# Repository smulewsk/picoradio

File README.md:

<p align="center">
  <picture>
    <source media="(prefers-color-scheme: dark)" srcset="docs/logo/logo.svg">
    
  </picture>
</p>
<p align="center"></p>

# Pico 2 W Internet Radio (FreeRTOS)

Pico Radio turns a Raspberry Pi Pico 2 W and a handful of cheap modules into a complete desktop radio. It plays internet radio stations, works as a Bluetooth speaker for your phone, and has a voice assistant you can talk to. Two knobs and a small colour display handle everyday use. A web page on your phone or computer does the rest: pick stations, edit the list, change settings and update the firmware.

**Three sources, one radio:**
- **Internet radio:** MP3 and AAC/AAC+ streams over HTTP and HTTPS, with song titles from the stream. Up to 31 stations of your own, with playlist import and export.
- **Bluetooth:** pair your phone and play its music through the radio, with artist, title and play/pause/next on the knobs.
- **AI assistant:** switch to *AI Gemini*, ask a question out loud, and hear the answer through the speaker. It uses Google's Gemini Live API on the free tier, in English or another language you choose.

**Hardware:** a Pico 2 W, a PCM5102 I2S DAC for line-level audio, a 2.25" ST7789 display (284×76), two rotary encoder modules (KY-040, or the ones labelled S1 / S2 / KEY) and, for the AI, an INMP441 microphone. Everything runs on 5 V from USB. Each module connects with a few jumper wires; see [Wiring](#wiring).

**Everyday use:**
- **Remembers you:** the radio starts on the last station at the last volume.
- **Web setup:** WiFi, names, the Gemini key and voice are set from the web page, with no rebuilding.
- **Safe updates:** firmware updates go over WiFi into a spare flash slot. If a new version fails to start, the radio falls back to the previous one.

## Screenshots

**Internet radio:** station, song title from the stream, codec, bitrate and a stereo VU meter.

**Bluetooth:** your phone's music, with artist and title.

**AI Gemini:** the spoken answer also scrolls on the display.

<p align="center"><em>The prototype on a breadboard: Pico 2 W, PCM5102 DAC with RCA outputs, two encoders, the INMP441 microphone and the display.</em></p>

## Under the hood

The firmware is written in C on FreeRTOS, using both cores of the RP2350. It was built for the Pico 2 W:

- **FreeRTOS SMP** on both cores
- **lwIP sockets** over WiFi, **HTTP and HTTPS** + Shoutcast/Icecast **ICY metadata** (song titles), redirects, **.pls / .m3u playlist links**
- **MP3 decoding** with [minimp3](https://github.com/lieff/minimp3) (32–320 kbps, mono or stereo, any sample rate)
- **AAC and HE-AAC (AAC+) decoding** with the Helix AAC decoder, for `audio/aac` and `audio/aacp` streams (ADTS)
- **PCM5102** I2S DAC driven by PIO + DMA
- **ST7789 2.25" 76×284** TFT (landscape 284×76), DMA framebuffer, SPI through PIO (any pins)
- **2 rotary encoders**: volume and station
- **Web remote**: control page at **http://picoradio.local** with a live copy of the display, a station editor and a **settings page** (WiFi, Gemini key, names... no rebuild needed)
- **WiFi setup network**: without a working WiFi the radio opens its own network (`picoradio`), and a phone that joins it lands on the settings page
- **Firmware updates over WiFi** from the web page, with automatic fallback to the previous firmware
- **Remembers** the last station and volume across power-off
- **AI voice assistant**: talk to Google Gemini through an **INMP441** microphone and hear the spoken answer on the radio (Gemini Live API, free tier). English by default, or any other language set on the web page; it greets you when you switch to it
- **Bluetooth audio (A2DP sink)**: stream from your phone. AVRCP shows the artist and title, encoder 2 controls play/pause and next track, and volume stays in sync with the phone

| Core | Task | Job |
|---|---|---|
| 0 | `net` | WiFi, HTTP/HTTPS, playlists, ICY demux → 48 KB stream buffer |
| 0 | `ui` | encoders, screen at 25 fps, saves station / volume |
| 0 | `web` | HTTP server (port 80) for the web remote, settings and firmware updates, mDNS `picoradio.local` |
| 0 | `rssi` | reads the WiFi signal strength every 3 s (lowest priority, so it never holds up the screen) |
| 1 | `dec` | MP3 / AAC → PCM (radio) or PCM passthrough (Bluetooth, AI), volume, VU levels, 6×1152-frame I2S buffers (DMA IRQ) |
| any | CYW43 / BTstack | WiFi driver, Bluetooth stack, SBC decoding |

In AI mode the `net` task also runs the microphone and the secure WebSocket (mbedTLS) connection to Gemini.

## Wiring

The diagram shows the Pico from the top, USB up, with its real pin order. Power and ground are drawn as labels: connect every **3V3** label to pin 36, **5V** to pin 40 (VBUS) and **GND** to any GND pin. `docs/make_wiring.py` redraws it if you change pins.

| Module pin | Pico 2 W | Physical pin |
|---|---|---|
| **PCM5102 DAC** | | |
| BCK | GP11 | 15 |
| DATA (DIN) | GP10 | 14 |
| LRCK (LCK) | GP9 | 12 |
| GND | GND | 13 (next to GP9) |
| SCK, if the board has it | GND | any GND (or bridge its SCK pad) |
| VCC / VIN | VBUS (5 V) | 40 |
| **ST7789 2.25" TFT** | | |
| BL / BLK (backlight) | GP12 | 16 |
| CS | GP13 | 17 |
| DC | GP14 | 19 |
| RST / RES | GP15 | 20 |
| SCL / SCK | GP16 | 21 |
| SDA / MOSI | GP17 | 22 |
| VCC | 3V3 | 36 |
| GND | GND | 18 or 23 |
| **INMP441 microphone** | | |
| SCK | GP18 | 24 |
| WS | GP19 | 25 |
| SD | GP20 | 26 |
| L/R (selects the left channel) | GND | any GND |
| VDD | 3V3 | 36 |
| GND | GND | 23 or 28 |
| **Encoder 1: source** | | |
| CLK (A) / S1, DT (B) / S2, SW / KEY | GP2, GP3, GP4 | 4, 5, 6 |
| **Encoder 2: volume + stations** | | |
| CLK (A) / S1, DT (B) / S2, SW / KEY | GP5, GP6, GP7 | 7, 9, 10 |
| **Both encoders** | | |
| + / VCC / 5V | **3V3** (even if the pin says 5V; required) | 36 |
| GND | GND | 3 or 8 |

Tips:
- **Power:** use a decent USB charger and cable. VBUS (pin 40) should read 4.75–5.25 V; a weak supply (below ~4.5 V) gives noise in the audio. Powering the DAC from 5 V lets its own regulator make a clean 3.3 V.
- **Display wires:** keep SCL and SDA short (under ~10 cm) with a GND wire next to them. Long loose wires at 37.5 MHz can corrupt the picture; then lower `TFT_SPI_HZ`.
- **Display backlight:** some modules light up when BL is *low*: set `TFT_BL_ACTIVE_LOW 1` (the default here) or 0 for modules that light up on high. If the backlight comes on at power-on and then fades out, this is the setting to flip.
- **Encoders:** modules are labelled either CLK / DT / SW or S1 / S2 / KEY: same thing.
  - **Power:** the + pin **must** go to 3V3 (not 5V). S1 / S2 are read as plain inputs (`ENC_AB_PULLUP 0`) and rely on the module's own pull-up resistors, which hang off that pin; the Pico's inputs aren't meant for 5 V. If + is left open, S1 / S2 sit at a half level and turning does nothing.
  - **Missing pull-up on a module:** if one line stays at 0 (a resistor missing or broken), solder 10 kΩ from that pin to +, or set `ENC_AB_PULLUP 1` to add the Pico's internal pull-ups (fine once + is on 3V3).
  - **Direction:** `ENC1_REVERSE` / `ENC2_REVERSE` (both 1 here, which suits these modules). Backwards → flip the setting or swap S1 and S2.
  - **Steps:** one click moves two steps (or two clicks one step) → `ENC_STEPS_PER_DETENT` 2 instead of 4.
  - The encoders are sampled 2000 times a second (not on interrupts), so a bad contact can't stall the radio.
- **Display colours:** inverted colours (yellow shows as blue, green as purple) → toggle `TFT_INVERT`. Red and blue swapped → toggle `TFT_BGR`.

**PCM5102 module jumpers.** Small boards with only BCK / DATA / LRCK / GND / VCC pins have these set already, so skip this. On boards with pads on the back (GY-PCM5102), solder them like this, or you get no sound:

| Jumper | Setting |
|---|---|
| H1L (FLT) | **L** |
| H2L (DEMP) | **L** |
| H3L (XSMT) | **H** (un-mute) |
| H4L (FMT) | **L** (I2S) |

Also bridge the SCK pad on the front to GND, or wire SCK to GND.

You can change any pin in `include/config.h`. The three DAC pins and the six display pins can be any GPIOs, in any order: both are driven by PIO programs (`src/i2s.pio`, `src/tft_spi.pio`), not the SPI/I2S hardware blocks. The mic's WS must stay at SCK + 1.

### Breakout board (PCB)

Instead of a breadboard, `hardware/picoradio-breakout/` has a KiCad 8 project for a 61 × 71 mm carrier board, with ready-to-order Gerbers for JLCPCB. It has a socket for the Pico 2 W, a labelled goldpin header for each module (DAC, display, both encoders, microphone), a power header (USB 5 V, 3V3, GND) and a header for the spare GPIOs; the bottom layer is a GND plane. The pins match the table above, so the firmware runs unchanged. See [its README](hardware/picoradio-breakout/README.md).

## Configure

Most settings are changed on the radio's web page (**Settings** card, see [Settings page](#settings-page)) and kept in flash. `include/config.h` holds the hardware setup and the **factory defaults** for those settings:

- **Factory defaults** (all changeable later on the web page): `WIFI_SSID` / `WIFI_PASSWORD`, `WEB_HOSTNAME`, `BT_DEVICE_NAME`, `RADIO_TLS_VERIFY`, `GEMINI_API_KEY` (free at <https://aistudio.google.com/apikey>), `GEMINI_MODEL`, `GEMINI_VOICE`, `AI_LANGUAGE` (`"English"`, any other language name, or `"auto"`), `AI_GREETING`, `AI_SYSTEM_PROMPT`.
- **WiFi for the first start:** put your network in `WIFI_SSID` / `WIFI_PASSWORD` (or pass them to CMake, below). Or leave them as they are: the radio then opens its [setup network](#wifi-setup-access-point) and you enter the WiFi on the page.
- **Setup network:** `AP_SSID`, `AP_PASSWORD` (8+ characters, `""` = open), `AP_AFTER_FAILS`, `AP_IDLE_MIN`.
- `STATIONS[]`: the **factory** station list (edit stations later on the web page). Each entry is a name and URL. A URL can be:
  - an `http://` or `https://` MP3, AAC or AAC+ stream, or
  - a link to a `.pls` or `.m3u` playlist (what many station websites offer). The radio plays the first stream in it.

  Ogg/Opus, FLAC, MP4/LATM and HLS (`.m3u8`) streams are not supported, and the screen says so when it hits one.
- **Pins:** `PIN_*`. See [Wiring](#wiring).
- **Display:** the offsets, `TFT_MADCTL` (0x60, or 0xA0 to flip it 180°), `TFT_BGR`, `TFT_INVERT`, `TFT_BL_ACTIVE_LOW`, `TFT_SPI_HZ`.
- **Encoders:** `ENC_STEPS_PER_DETENT` (try 2 if one click moves two steps), `ENC1_REVERSE` / `ENC2_REVERSE`, `ENC_AB_PULLUP` (Pico pull-ups on S1 / S2; 0 = the module's own). See the encoder tips under [Wiring](#wiring).
- **Audio:** `VOLUME_DEFAULT`, the level trims `TRIM_RADIO_DB` / `TRIM_BT_DB` / `TRIM_AI_DB` (see [Notes](#notes-and-ideas)), `MIC_GAIN`.
- **Bluetooth:** `BT_SECURE_CONNECTIONS` (see [Bluetooth](#bluetooth)).

## Build

You need the Pico SDK 2.x and the ARM toolchain. The VS Code Pico extension installs both in `~/.pico-sdk`.

```bash
git clone https://github.com/<your-account>/picoradio.git
cd picoradio
./setup.sh          # fetches FreeRTOS, minimp3 and Helix AAC into lib/
```

```bash
cmake -S . -B build -G Ninja -DPICO_TOOLCHAIN_PATH=$HOME/.pico-sdk/toolchain/14_2_Rel1
```

```bash
cmake --build build
```

You can also pass the factory WiFi and API key at build time instead of writing them into `config.h`:

```bash
cmake -S . -B build -G Ninja -DWIFI_SSID="MyWiFi" -DWIFI_PASSWORD="secret" -DGEMINI_API_KEY="AIza..."
```

The build makes `build/pico_radio.uf2` (the firmware) and `build/pt.uf2` (the flash partition table, needed once).

To flash: hold BOOTSEL, plug in the USB cable, and copy `build/pico_radio.uf2` onto the RP2350 drive. Debug output goes to the USB serial port (the Pico shows up as a serial device, e.g. `/dev/tty.usbmodem…` on a Mac; any baud rate). It reconnects after each restart, so reopen the serial monitor if it goes quiet.

**First time only (for updates over WiFi):** before `pico_radio.uf2`, copy `build/pt.uf2` onto the RP2350 drive. It writes the partition table with the two firmware slots (see [Firmware updates over WiFi](#firmware-updates-over-wifi-ota)). The radio then comes back as the RP2350 drive (if not, enter BOOTSEL again), and you copy `pico_radio.uf2` as usual. Your stations and the Bluetooth pairing stay. After that you can update from the web page.

If `PICO_SDK_PATH` isn't set, the build uses `~/.pico-sdk/sdk/2.3.0` (the VS Code extension's copy). Without any SDK installed, configure with `-DPICO_SDK_FETCH_FROM_GIT=on` (and `-DPICO_SDK_FETCH_FROM_GIT_TAG=2.3.0`) and CMake downloads it.

**VS Code tasks** (*Terminal → Run Task…*, or ⇧⌘B for *Compile Project*):

| Task | Does |
|---|---|
| Compile Project | `ninja -C build` |
| Compile & OTA Flash | build, then send `pico_radio.uf2` to the radio over WiFi |
| OTA Flash (curl) | only the WiFi upload ([OTA](#firmware-updates-over-wifi-ota)) |
| Compile & Flash (USB) | build, then load over USB with picotool |
| Run Project | load over USB with picotool |

The OTA tasks ask for the radio's address (Enter = `picoradio.local`; use the IP if `.local` doesn't resolve, or `192.168.4.1` in [setup mode](#wifi-setup-access-point)). To give a task its own shortcut, add it to your keyboard shortcuts (⇧⌘P → *Preferences: Open Keyboard Shortcuts (JSON)*):

```json
{ "key": "cmd+alt+u", "command": "workbench.action.tasks.runTask", "args": "Compile & OTA Flash" }
```

## Controls

**Encoder 1 picks the source.** Turn it to open the picker (*Internet Radio* / *Bluetooth* / *AI Gemini*), then push to switch. When the picker is closed, a push mutes.

**Encoder 2 sets volume and picks stations.** Turning it always changes the volume, unless the station list is open.

| | Turn | Push | Long push (0.7 s) |
|---|---|---|---|
| Encoder 1 | Open the source picker / move in it | Switch to the picked source (picker closed: mute on/off) | Info screen (IP, RSSI, heap, underruns) |
| Encoder 2 (radio) | Volume (moves in the list while it is open) | Open the station list / tune to the highlighted station | Reconnect |
| Encoder 2 (Bluetooth) | Volume (synced with the phone) | Play / pause | Next track |
| Encoder 2 (AI) | Volume | Microphone on / off | Start a new conversation |

**Holding encoder 1 pressed while switching on** starts the radio with the factory settings from `config.h` (for when a wrong WiFi password locks you out). **Holding encoder 2** while switching on, or pressing it in the first 2 seconds while the logo shows, opens the [setup network](#wifi-setup-access-point) instead.

Lists close by themselves after 6 seconds without input. A `*` marks what is playing now. Switching from Bluetooth back to *Internet Radio* returns to the last station you listened to.

## Bluetooth

1. Turn encoder 1 to **Bluetooth** and push. The header turns blue and the screen shows *BT WAITING FOR PHONE*.
2. On the phone, open Bluetooth settings and pair with **Pico Radio** (change the name on the web page under Settings). There is no PIN: the radio accepts the pairing by itself.
3. Play music on the phone. The screen shows the artist and title.

The pairing is saved in flash. Next time you pick Bluetooth, the radio tries to reconnect to the last phone by itself.

When you switch back to *Internet Radio* with encoder 1, the radio disconnects the phone, hides itself from Bluetooth, and goes back to WiFi streaming. Bluetooth is only visible while the Bluetooth source is selected.

Pairing problems:
- **"Pairing failed" on the phone (status `0x05` in the log):** in the web page's Bluetooth panel press **Forget paired phones**, on the phone choose *Forget this device* and switch Bluetooth off and on, then pair again.
- `BT_SECURE_CONNECTIONS` (config.h) allows the newer "Secure Connections" pairing. It's on here; set it to 0 if a phone fails to pair.

Notes:
- Only the SBC codec is supported. Every phone supports it, and A2DP always falls back to it.
- The phone's clock and the Pico's audio clock drift apart a little. The decoder keeps about 0.1–0.25 s of audio buffered and drops a few samples when the buffer gets too full. You shouldn't hear it.
- WiFi stays connected in Bluetooth mode, so switching back to a station is fast.

## AI voice assistant (Gemini)

1. Get a free Gemini API key at <https://aistudio.google.com/apikey> and enter it on the web page (**Settings → AI Gemini → API key**). No rebuild needed.
2. Turn encoder 1 to **AI Gemini** and push. The header turns purple. After about a second Gemini greets you (switch this off under Settings → Greeting) and the screen shows **AI LISTENING** with a microphone level meter.
3. Just talk, in the language set under Settings (English by default), e.g. *"What is the capital of Australia?"*. When you stop, Gemini answers out loud. The screen shows what you said (`You: ...`) and then the answer (`AI: ...`).
4. Keep talking. It remembers the conversation until you leave AI mode or long-press encoder 2.

How it works:
- The INMP441 is read at 32 kHz by a PIO program and filtered down to 16 kHz.
- 100 ms audio chunks go over a secure WebSocket (TLS, verified against Google's root certificates) to the Gemini Live API, model `gemini-3.8-live` (changeable under Settings).
- **Language and voice:** set under Settings. The radio adds "Always answer in <language>" to the instructions, or "answer in the language the user speaks" for *Automatic*. There are 30 voices (Kore, Puck, Charon, ...); the field suggests them.
- Gemini detects when you have finished speaking, then streams its voice back as 24 kHz PCM. That audio plays through the same output and volume control as the radio.
- **Half-duplex:** the microphone is muted while the answer plays, so the radio doesn't hear itself. You can't interrupt an answer; wait for *AI LISTENING*.
- Push encoder 2 to turn the microphone off (*AI MIC OFF*), for example while people are talking nearby.
- Gemini ends sessions after about 15 minutes. The radio reconnects by itself, and that starts a new conversation.

**Controlling the radio by voice.** Gemini can work the radio for you through function calls:

| Say, for example | What happens |
|---|---|
| "Play RMF FM", "put on some jazz", "play a Polish news station" | `play_station`: looks in your saved stations first, then searches **radio-browser.info** (a free directory of ~50,000 stations). Gemini says what it found in one sentence, then the radio switches to it and AI mode ends. |
| "Save this station", "add Radio Nowy Świat to my stations" | `add_station`: saves the station just played (or searches for one) to your list. |
| "Remove RMF Classic from my stations" | `remove_station` |
| "What stations do I have?" | `list_saved_stations` |
| "Turn it down to 30 percent" | `set_volume` |

- A station found in the directory plays without being added to your list: the screen shows `NEW` instead of the station number, and the web page says *Found by AI*. Say "save it" (in AI mode) to keep it.
- Only stations the radio can play are picked: MP3 or AAC/AAC+ over HTTP(S), not HLS or Ogg. The most popular match wins; Gemini mentions a few others.
- The directory is searched over plain HTTP (the radio's single TLS connection is busy with Gemini), from the `de1`, `nl1` or `at1.api.radio-browser.info` mirrors. Only the search words go there.
- The serial log shows every call: `[ai] function play_station(...)` and its result.

Notes:
- **Privacy:** while *AI LISTENING* is shown, everything the microphone hears is sent to Google. On the free tier, Google may use the data to improve its products. Switch to another source, or push encoder 2, to stop listening.
- If the meter barely moves when you speak, raise `MIC_GAIN` (default 16 = +24 dB). If it is often red, lower it.
- The free tier has rate limits. If you hit them, the screen shows a connection error and the radio retries every few seconds.

## Web remote

Open **http://picoradio.local** on a phone or computer on the same WiFi. If your device doesn't support `.local` names (some Android phones), use the IP address shown on the info screen (long-press encoder 1).

What the page shows and does:
- **Live display:** a pixel-exact copy of the TFT, up to ~15 frames per second (compressed, and skipped when nothing changed).
- **Now playing:** station, song title with proper Polish letters (the TFT itself uses plain ASCII), and the stream parameters.
- **Source:** Internet Radio, Bluetooth or AI Gemini.
- **Volume and Mute:** synced with the knobs and, in Bluetooth mode, with the phone.
- **Radio:** a station list and Reconnect. **Bluetooth:** Previous, Play/Pause and Next. **AI:** microphone on/off, a new conversation, and the mic level.
- **Edit stations:** add, rename, change the URL, reorder (↑ ↓) and delete. Changes are saved on the radio and survive power-off.
- **Import and export:** import an `.m3u`, `.m3u8` or `.pls` playlist (you see a preview, then choose *Append* or *Replace all*), or export the list as `.m3u` / `.pls`.
- **Settings:** WiFi, names, the Gemini key, voice, language and more. See [Settings page](#settings-page).
- **Firmware:** the version, build time and slot, and updates over WiFi. See [Firmware updates](#firmware-updates-over-wifi-ota).

### Stations

**The last station and the volume are remembered** across power-off. They're saved 5 s after you stop changing them, so browsing or turning the knob doesn't wear out the flash. They're kept in their own flash sector (below the stations, outside the firmware slots), so OTA updates keep them too. Mute isn't saved, and Bluetooth / AI mode always start back on the radio.

- **Storage:** up to 31 stations, kept in flash. Names can be up to 47 bytes (Polish letters fine; the TFT shows them without accents), URLs up to 207 characters.
- **Factory list:** the stations in `config.h`. They are used until you first edit the list. *Reset to defaults* brings them back.
- **Power cuts:** each save writes the whole list to the second of two flash slots and only then switches to it, so a power cut during a save keeps the previous list.
- **Saving pauses the music:** a flash write briefly stops both processor cores, so playback pauses for about 0.1 s.
- **Import:** reads names and URLs from `#EXTINF` (M3U) or `File`/`Title` (PLS) lines. Entries that aren't `http(s)` are skipped. HLS entries are imported, but say "not supported" when played.
- **Export:** `http://picoradio.local/stations.m3u` also opens directly in VLC, so the same list plays on your computer.
- **Playing station:** if you delete or move the station that's playing, it keeps playing under its new position. Changing its URL reconnects it.

The page lives in `web/index.html` and is built into the firmware, gzip-compressed; CMake regenerates `web_page.h` when you edit it. The radio's name (`picoradio`) is set under Settings.

API, for scripts or Home Assistant. `/api/cmd` and every POST need the header `X-Pico-Radio: 1`, e.g. `curl -H "X-Pico-Radio: 1" "http://picoradio.local/api/cmd?a=vol&v=20"`:

| Request | Effect |
|---|---|
| `GET /api/status` | JSON: source, station, title, state, codec, kbps, rate, volume, mute, buffer, RSSI, VU levels, mic level, firmware version / build time / slot |
| `GET /api/screen.bmp` | the current display as a 284×76 BMP |
| `GET /api/screen.rle?h=..` | the display run-length coded, as the page uses it (a few KB); `204` if it hasn't changed since the frame with hash `h`. Format in `src/web.c` |
| `GET /api/cmd?a=tune&v=3` | play station 4 (0-based) |
| `GET /api/cmd?a=source&v=radio\|bt\|ai` | switch source |
| `GET /api/cmd?a=vol&v=20` | set volume (0–32) |
| `GET /api/cmd?a=mute` / `play` / `next` / `prev` / `mic` / `reload` | toggle mute, Bluetooth playback, AI mic, reconnect or new conversation |
| `GET /api/cmd?a=btforget` | delete all paired phones (also the "Forget paired phones" button in Bluetooth mode) |
| `GET /api/cmd?a=restart` | restart the radio |
| `GET /api/config`, `POST /api/config` | read / save the settings (see [Settings page](#settings-page)) |
| `GET /api/stations` | JSON: `{"max":31,"default":false,"list":[{"name":..,"url":..}]}` |
| `POST /api/stations` (form) | `a=add&name=..&url=..`, `a=edit&i=..&name=..&url=..`, `a=del&i=..`, `a=up&i=..`, `a=down&i=..`, `a=reset`, `a=import&mode=append\|replace&data=<name TAB url per line>` |
| `GET /stations.m3u`, `GET /stations.pls` | the station list as a playlist |
| `POST /api/ota` (raw body) | firmware update with `build/pico_radio.uf2` or `.bin`; the radio restarts on it. Reply: `{"ok":true,"slot":"B"}` or `{"ok":false,"error":".."}` |

There is no password: anyone on your WiFi can control the radio, and update its firmware. Keep it on a home network you trust. Other web sites open in your browser can't: everything that changes something (uploads, settings, station edits, `/api/cmd`) must carry the header `X-Pico-Radio: 1`, which only the radio's own page, the VS Code tasks and your own scripts send. Add `-H "X-Pico-Radio: 1"` when you use `curl`.

## Settings page

The **Settings** card on the web page changes, without rebuilding:

| Group | Settings |
|---|---|
| WiFi | network name, password, the radio's name (`http://<name>.local`) |
| Bluetooth | the name the phone sees |
| AI Gemini | API key, model, voice (list of the 30 voices), answer language (or automatic), greeting on/off, instructions (system prompt) |
| Stations | check HTTPS certificates |

- **Saving:** settings are kept in flash, outside the firmware slots, so OTA updates keep them. Two copies are written alternately, so a power cut while saving keeps the previous settings.
- **When changes apply:** Gemini settings apply at the next AI conversation (right away if AI is playing). WiFi and the names apply after a restart; the page offers a *Restart now* button.
- **Secrets:** the WiFi password and the API key are never sent back to the page, which only shows whether they are set. Leave the field empty to keep the saved one.
- **Defaults:** the values in `include/config.h` are the factory defaults. *Factory settings* goes back to them.
- **Locked out?** If the radio can't join WiFi any more (a typo in the password, a new router), it opens the [setup network](#wifi-setup-access-point) after 3 failed tries, or right away when **encoder 2** is held while switching on. Holding **encoder 1** instead starts with the `config.h` settings and erases the saved ones.
- **Open network / removing the key:** tick *Open network (no password)* for a WiFi without a password, or *Remove the saved key* to delete the Gemini key.
- **API:** `GET /api/config`, `POST /api/config` (form fields `ssid pass clearpass hostname btname key clearkey model voice lang greet prompt tls`, or `a=reset`), `GET /api/cmd?a=restart`. POSTs and `/api/cmd` need the `X-Pico-Radio: 1` header.

Pins and display options stay in `config.h`: they need different wiring anyway.

### WiFi setup (access point)

When the radio has no WiFi to join, it opens its own network so you can set it up from a phone:

1. **When it opens:** no WiFi set yet (the `config.h` placeholder), the network can't be joined 3 times in a row after power-on (`AP_AFTER_FAILS`), or **encoder 2 held** while switching on (pressing it within the first 2 seconds, while the logo shows, works too). The screen shows **WIFI SETUP** and *Join WiFi picoradio, open 192.168.4.1*.
2. **Join it:** network `picoradio`, no password (`AP_SSID` / `AP_PASSWORD`). Most phones then open the radio's page by themselves; otherwise go to <http://192.168.4.1>.
3. **Enter your WiFi** in the Settings card (it opens by itself) and press **Save**. The radio restarts and joins your network, and the page is at `http://picoradio.local` again.

- **Open network:** without a password anyone nearby can join while it's open and change the settings. Set `AP_PASSWORD` (8+ characters) if that matters.
- **Bluetooth** still works while the setup network is open; internet radio and AI need your WiFi.
- **A WiFi that worked before** (router restarting) is retried forever and never opens the setup network. If the setup network was opened by failures and nobody joins it within 10 minutes (`AP_IDLE_MIN`), the radio restarts and tries your WiFi again.

## Firmware updates over WiFi (OTA)

**Version.** The firmware version is set in `CMakeLists.txt`: `project(pico_radio VERSION 1.0.0 ...)`. Bump it when you release a change. Every build also records its build time. Both show on the Firmware card and at the bottom of the web page, in the top line of the info screen (long-press encoder 1), in the serial log at boot, and in `picotool info`. `GET /api/status` has them as `ver` and `built`.

The web page has a **Firmware** card: pick `build/pico_radio.uf2` (a `.bin` works too) and the radio writes it into its spare flash slot, then restarts on it. The display shows the progress. The internet stream (and the AI) pause meanwhile, so the upload gets the whole WiFi link; Bluetooth keeps playing, muted. If the update fails, the stream resumes. The page waits for the radio to come back and tells you which slot it runs from.

From the command line:

```bash
curl --data-binary @build/pico_radio.uf2 -H "Content-Type: application/octet-stream" -H "X-Pico-Radio: 1" http://picoradio.local/api/ota
```

In VS Code, the *Compile & OTA Flash* task does the build and this upload in one go (see [Build](#build)).

How it works. It uses the RP2350 boot ROM's own A/B partitions, so there's no extra bootloader:

- **Two slots.** `pt.json` splits the flash into slot A and slot B of 1984 KB each (the firmware is about 830 KB). The last 120 KB stay outside the slots, for the settings, the stations, the last station / volume and the Bluetooth pairing, so updates don't touch them.
- **Safe writing.** The update goes into the slot that isn't running. Its first sector is erased first and written last, so a slot never holds half a firmware that could boot. A broken upload (WiFi drop, wrong or cut-off file, UF2 for another chip) is refused and the radio keeps running as before.
- **Try before you buy.** The new firmware is marked "TBYB" while it's written, and the radio restarts with a flash-update boot, which lets the boot ROM run it once. It confirms itself once the web server is up (or after 12 s without WiFi), and only then is it kept. If it crashes or hangs before that, switch the radio off and on: the boot ROM starts the previous firmware again.
- **After the confirm** the old slot is wiped, so normal boots always pick the new firmware. The next update goes there.
- **Size check.** The build fails if the firmware outgrows a slot. Change both sizes in `pt.json` if you ever need more (and flash `pt.uf2` again).

Things to know:
- **Without the partition table** (an old install, or flashed over SWD) the radio works normally, but the Firmware card says updates need `pt.uf2`. The info screen and the web page show the slot (`FW slot A` / `B`, or `-` without a partition table).
- **Flashing over USB still works.** Copying `pico_radio.uf2` onto the BOOTSEL drive puts it into a slot too, and it's kept the same way.
- **SWD (the VS Code "Flash" task / OpenOCD)** writes the `.elf` at the start of flash and overwrites the partition table. Copy `pt.uf2` and `pico_radio.uf2` again over USB afterwards.
- **There's no signature check:** the radio accepts any RP2350 Arm firmware from your network.

More screenshots are in `docs/screenshots/web/`. They were taken in a browser on a computer, with a stand-in for the radio that serves the same page and API and display frames drawn by the radio's own display code.

## Troubleshooting

| Symptom | Check |
|---|---|
| Screen shows PLAYING, VU moves, but no sound | DAC wiring (BCK GP11, DATA GP10, LRCK GP9). On the DAC: SCK pad to GND, XSMT high (un-muted). Volume not at 0, not muted. |
| Hiss, buzz or crackle | VBUS below ~4.5 V: better charger / cable. DAC on 5 V (VBUS). Short wires, GND next to the signal wires. Mute test: noise while muted = electrical; only while playing = the stream (watch the underrun counter on the info screen). |
| Backlight on at power-on, then fades to dark | `TFT_BL_ACTIVE_LOW` the wrong way round for your module. |
| Wrong colours on the display | `TFT_INVERT` (inverted colours) or `TFT_BGR` (red/blue swapped). |
| Garbage or shifted lines on the display | Long display wires: shorten them or lower `TFT_SPI_HZ`. |
| First WiFi attempt fails, second works | Normal now and then; the radio retries by itself. The log says why (`timeout`, `wrong password`, ...). |
| Can't reach the radio after changing WiFi | It opens the `picoradio` network after 3 failed joins (or hold encoder 2 while switching on): join it and fix the WiFi. Holding encoder 1 goes back to the `config.h` settings. |
| Encoder push works, turning does nothing | The module's + pin isn't on 3V3. With + connected, one line stuck at 0 means a missing pull-up on the module: 10 kΩ from it to +, or `ENC_AB_PULLUP 1`. |
| Encoder turns the wrong way | `ENC1_REVERSE` / `ENC2_REVERSE`. |
| Phone won't pair (`status 0x05`) | *Forget paired phones* on the web page, forget the radio on the phone, pair again. See [Bluetooth](#bluetooth). |
| `TLS handshake failed` on an https station | The log shows the reason. Try the station's `http://` address, or untick *Check station certificates* if it's an unknown CA. |
| AI says "Set the Gemini API key" | Enter the key under Settings → AI Gemini. |
| Update fails / is slow | The log shows `[ota]` lines. Updates need `pt.uf2` flashed once over USB. |

## HTTPS stations

HTTPS works for radio streams, playlists and redirects.

- **Certificates:** checked against 23 bundled root certificates from the Mozilla trust store (`src/ca_roots.h`): Let's Encrypt, DigiCert, Sectigo/USERTrust, GlobalSign, Google, Amazon, Microsoft, GoDaddy/Starfield and the Polish CA Certum. Roots stay in flash and are parsed only when a server's chain names them, so the bundle costs 21 KB of flash and almost no RAM.
- **Tested from a computer** with this exact TLS code: SomaFM (playlist and AAC stream), Radio Paradise, Polskie Radio, RMF FM, Google, GitHub, DigiCert, Certum, Microsoft and Cloudflare all verify.
- **"TLS: unknown cert authority":** the station uses a CA that isn't bundled. Untick *Check station certificates* under Settings (or `RADIO_TLS_VERIFY 0`) to skip the check for radio streams; the audio is still encrypted. The Gemini connection always verifies, because it carries your API key.
- **Office networks:** a network with an HTTPS-inspecting firewall replaces the certificates, and verification fails. That is the check doing its job.
- **Memory:** a TLS connection needs about 47 KB while connecting and 28 KB while streaming. With AAC+ over HTTPS, TLS plus the AAC decoder need about 110 KB at once. That fits only because `src/mem.c` spreads big blocks over both heaps (FreeRTOS pool and C heap) with best-fit placement. The info screen (long-press encoder 1) shows both: `Free RTOS ..K  C ..K`.
- **Not checked:** certificate dates (the radio has no clock), and revocation.

## Screen (284×76)

```
| Station name                               3/6 |  <- header (blue / BT blue / AI purple)
| Artist - Song title (scrolls)                  |
| PLAY [MP3] 128kbps 44.1kHz ST     buf87% -58dBm|  <- state, codec, bitrate, rate, channels
| ▮▮▮▮▮▮▮▮▮▮▮▮▮▮▮▮▮ [L R] ▮▮▮▮▮▮▮▮▮▮▮▮▮▮▮▮▮▮▮    |  <- stereo VU meters, L <- centre -> R
| 0  5 10  20  30    dB    30  20 10  5  0       |
```

- **VU meters:** 20 LED segments per channel covering -40 to 0 dB in 2 dB steps (green, then amber from -12 dB, then red from -6 dB). Peak markers hold for 0.8 s and then fall. They show the level of the audio as it leaves the speaker, measured before the volume control, so they move even at low volume.
- **Volume:** the volume bar replaces the meters for 2 s after any change (encoder, or the phone in Bluetooth mode), and stays while muted.
- **Stream parameters:** codec badge plus details. MP3: bitrate, sample rate, ST/MONO. SBC (Bluetooth): the real bitrate from the phone's bitpool, sample rate, JS/ST/MONO. PCM (AI): 16 bit, 24 kHz, MONO.

See `docs/screenshots/` for every screen.

## Logo

The logo files are in `docs/logo/`:
- `logo.svg` for dark backgrounds, `logo-light.svg` for light ones, and `icon.svg` (the badge alone; also the web page's favicon).
- PNG exports are in `docs/logo/png/`.

`make_logo.py` regenerates all three SVGs. It needs `pip install fonttools`. You can change the font, weight, size, letter spacing, whether the name is one word (`--joined`), and the symbol in the badge (`--symbol eq | eq-wifi | wifi | broadcast`):

```bash
python3 docs/logo/make_logo.py docs/logo/fonts/Inter-var.ttf --wght 800 --size 56 --tracking 2 --joined --symbol eq
```

After changing the SVGs, run these two scripts (macOS; they use `qlmanage` and `sips`):

```bash
python3 docs/logo/export_png.py
```

```bash
python3 docs/logo/make_splash.py
```

`export_png.py` writes transparent PNGs to `docs/logo/png/`. `make_splash.py` writes `src/splash_logo.h`, the boot screen bitmap: the logo at 268×70 in the display's own colour format, run-length coded to about 16 KB of flash.

At power-on the TFT shows the logo with the firmware version under it while the backlight fades in (it is PWM-controlled), holds it for 1.5 s while WiFi starts, then shows the radio screen. You can change the hold time with `SPLASH_HOLD_MS` in `src/ui.c`.

The lettering is stored as outlines, so the logo looks the same without the font installed. The font is Inter (ExtraBold), under the SIL Open Font License (`docs/logo/fonts/OFL-Inter.txt`).

## Notes and ideas

- **Loudness per source:** radio stations are mastered louder than music from a phone, so `TRIM_RADIO_DB` in `config.h` turns the radio down 6 dB to match Bluetooth. Change the three `TRIM_*_DB` values by ear (0 or negative). The VU meter uses the same trim (but not the volume), so equally loud sources read the same.
- **Flash map** (4 MB): partition table, slot A, slot B (1984 KB each), then settings (2 × 4 KB), last station / volume log (4 KB), stations (2 × 8 KB), Bluetooth pairings (8 KB) and a reserved sector. All the data areas sit outside the firmware slots.
- **Stutter:** WiFi power-save is turned off already. Check the RSSI, or raise `PREBUFFER_BYTES` in `src/radio.h`. The stream buffer is 48 KB, about 3 s at 128 kbps.
- **OTA from a URL:** the radio could fetch updates itself (from a GitHub release, say) with the same writer in `src/ota.c`; now you upload the file from the page.
- **Bluetooth AAC / aptX codecs:** not supported; Bluetooth uses SBC.
- **AAC details:** the format comes from the stream's `Content-Type` (anything with `aac` in it). The decoder needs about 80 KB of RAM: 29 KB from the FreeRTOS pool and 51 KB from the C heap, because neither heap has room for both. It is allocated only while an AAC station plays, and freed on any source change, so the AI mode still has the heap for TLS. HE-AAC v2 (parametric stereo) streams play, but in mono: Helix has no parametric-stereo decoder, so you hear the mono core with SBR. On the status line, the AAC bitrate is averaged from the frame sizes.
- **AAC CPU load:** HE-AAC is heavier than MP3. Helix's portable C path should fit comfortably on core 1 at 150 MHz, but I haven't measured it. Watch the underrun counter on the info screen.
- **Licences:** Pico Radio itself is MIT licensed (see [License](#license)). minimp3 is CC0. Helix AAC is RealNetworks RPSL/RCSL. Only its C sources from `arduino-libhelix` are used, not the GPL Arduino wrapper. Check both licences before you sell a product built on this.

## License

Pico Radio is released under the [MIT License](LICENSE): use it, change it and share it, also commercially, as long as the copyright notice stays. The libraries it uses keep their own licences, listed at the end of [LICENSE](LICENSE). Note the Helix AAC decoder (RealNetworks RPSL / RCSL) and BTstack (free on Raspberry Pi chips only).

## Support

If Pico Radio is useful to you, you can buy me a coffee: [**Donate with PayPal**](https://www.paypal.com/donate/?business=smulewsk%40gmail.com&no_recurring=0&item_name=Pico+Radio) (smulewsk@gmail.com). Thank you!

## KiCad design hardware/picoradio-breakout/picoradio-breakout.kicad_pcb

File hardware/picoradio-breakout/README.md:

# picoradio breakout board (KiCad 8)

A carrier board for the Raspberry Pi Pico 2 W with a 2.54 mm goldpin header for every module of the radio.
The pin assignment is the firmware's (`include/config.h`), so no code changes are needed.

## Connectors

| Header | Pins (pin 1 first, square pad) | Notes |
|---|---|---|
| **J1 ENC1** | GND, S1 (GP2), S2 (GP3), KEY (GP4), +3V3 | encoder module order; + is 3V3, not 5 V |
| **J2 ENC2** | GND, S1 (GP5), S2 (GP6), KEY (GP7), +3V3 | |
| **J3 DAC** | BCK (GP11), DATA (GP10), LRCK (GP9), GND, GND, +5V | PCM5102 module order; VCC from USB 5 V |
| **J4 PWR** | +5V, +5V, GND, GND, +3V3, +3V3 | supply pins: +5V = Pico VBUS (USB), +3V3 = Pico 3V3(OUT), max ~300 mA |
| **J5 EXP** | GP26, GP27, GP28, GP22, GP21, RUN | spare GPIOs; RUN to GND resets the Pico |
| **J6 MIC** | SD (GP20), WS (GP19), SCK (GP18), GND, VDD (+3V3), L/R (GND) | INMP441 |
| **J7 TFT** | BL (GP12), CS (GP13), DC (GP14), RST (GP15), SDA (GP17), SCL (GP16), VCC (+3V3), GND | the ST7789 module's order reversed, for a straight cable |

Every pin is labelled on the silkscreen.

## Board

- **Size:** 61 × 71 mm, 2 layers, 1.6 mm, four M3 mounting holes.
- **Top layer:** all the signals, plus the picoradio logo and the pin labels on the silkscreen.
- **Bottom layer:** a solid **GND plane**. Every GND pin connects to it through thermal spokes, so it's easy to solder. A few signals dip to the bottom for a short hop where they must cross (36 mm in total).
- **Revision:** printed on the silkscreen from the title block, via the `${REVISION}` text variable (*File → Page Settings → Revision* in the PCB editor), so changing it there updates the board. Now Rev 1.2 (1.1: 45° tracks; 1.2: castellation pads, GND plane, logo on top).
- **Tracks:** 0.4 mm, 0.2 mm clearance, all bends at 45°, 0.6 / 0.3 mm vias. Fine for any hobby PCB service.
- **Pico, two ways:** every Pico pin has a through-hole *and* a surface-mount pad under the castellated edge.
  - **Socket** it on two 1x20 female headers (removable), or solder pin headers.
  - **Solder it flat**: align the castellations over the long pads and solder each one from the side. It's lower and needs no headers. Tracks under the Pico are covered by solder mask and the vias are tented, so the Pico's test pads underneath don't touch them; a layer of Kapton tape under the Pico adds margin.
  - Don't do both, because the holes would fill with solder.
- **All through-hole:** only goldpin headers, nothing small to solder.

## Ordering at JLCPCB

The ready Gerbers are in `gerbers/picoradio-breakout-rev1.2-gerbers-jlcpcb.zip`.

1. Go to jlcpcb.com → *Order now* and upload the zip. The viewer shows both sides; check the logo and labels.
2. Settings: **2 layers**, 1.6 mm, any colour, HASL (lead-free if you like). Leave the rest at the defaults.
3. No assembly is needed (all through-hole).

The zip holds: top/bottom copper (`.gtl/.gbl`), solder mask (`.gts/.gbs`), silkscreen (`.gto/.gbo`), outline (`.gm1`), plated and non-plated drill files (`.drl`). They were generated from the board data by `generator/gerbers.py` and checked by reading them back (`generator/gerber_check.py`):
- every hole sits in copper on both layers;
- the GND plane reaches all 17 GND pins as one area, with no floating copper;
- no other pin touches the plane;
- no silkscreen lies on a pad.

If you change the board in KiCad, export new Gerbers from KiCad instead: press **B** to fill the GND plane, then *File → Fabrication Outputs → Gerbers* (and *Drill Files*), and zip them.

## Files

| File | |
|---|---|
| `picoradio-breakout.kicad_pro` | open this in KiCad 8 |
| `picoradio-breakout.kicad_sch` | schematic |
| `picoradio-breakout.kicad_pcb` | routed PCB |
| `picoradio.kicad_sym`, `picoradio.pretty/` | project libraries: Pico 2 W symbol and footprint (holes + castellation pads), 1x08 row header |
| `gerbers/` | ready-to-order Gerber + drill zip for JLCPCB |
| `docs/` | previews of the board (rendered from the Gerbers) and the schematic |
| `generator/` | Python scripts that made the board (placement, router, checks) |

## Checks worth doing in KiCad

1. Open the project in KiCad 8 and press **B** in the PCB editor to fill the GND plane.
2. Run **Inspect → Design Rules Checker**. The board was checked with the generator's own clearance and connectivity checks, but not yet in KiCad itself.
3. Check the module pin orders against your modules (DAC, TFT, encoders, microphone). Clones differ. Swap the pins on the board or in the cable if yours differ.
4. Order with the ready zip (above), or export your own Gerbers after changes.

To regenerate after changing `generator/design.py` (pins, header positions): `python3 run_route.py && python3 chamfer.py && python3 write_kicad.py && python3 verify_files.py && python3 gerbers.py && python3 gerber_check.py` in `generator/` (needs Python 3 with matplotlib for the previews). The new files land in `generator/out/`; copy them over the ones here.

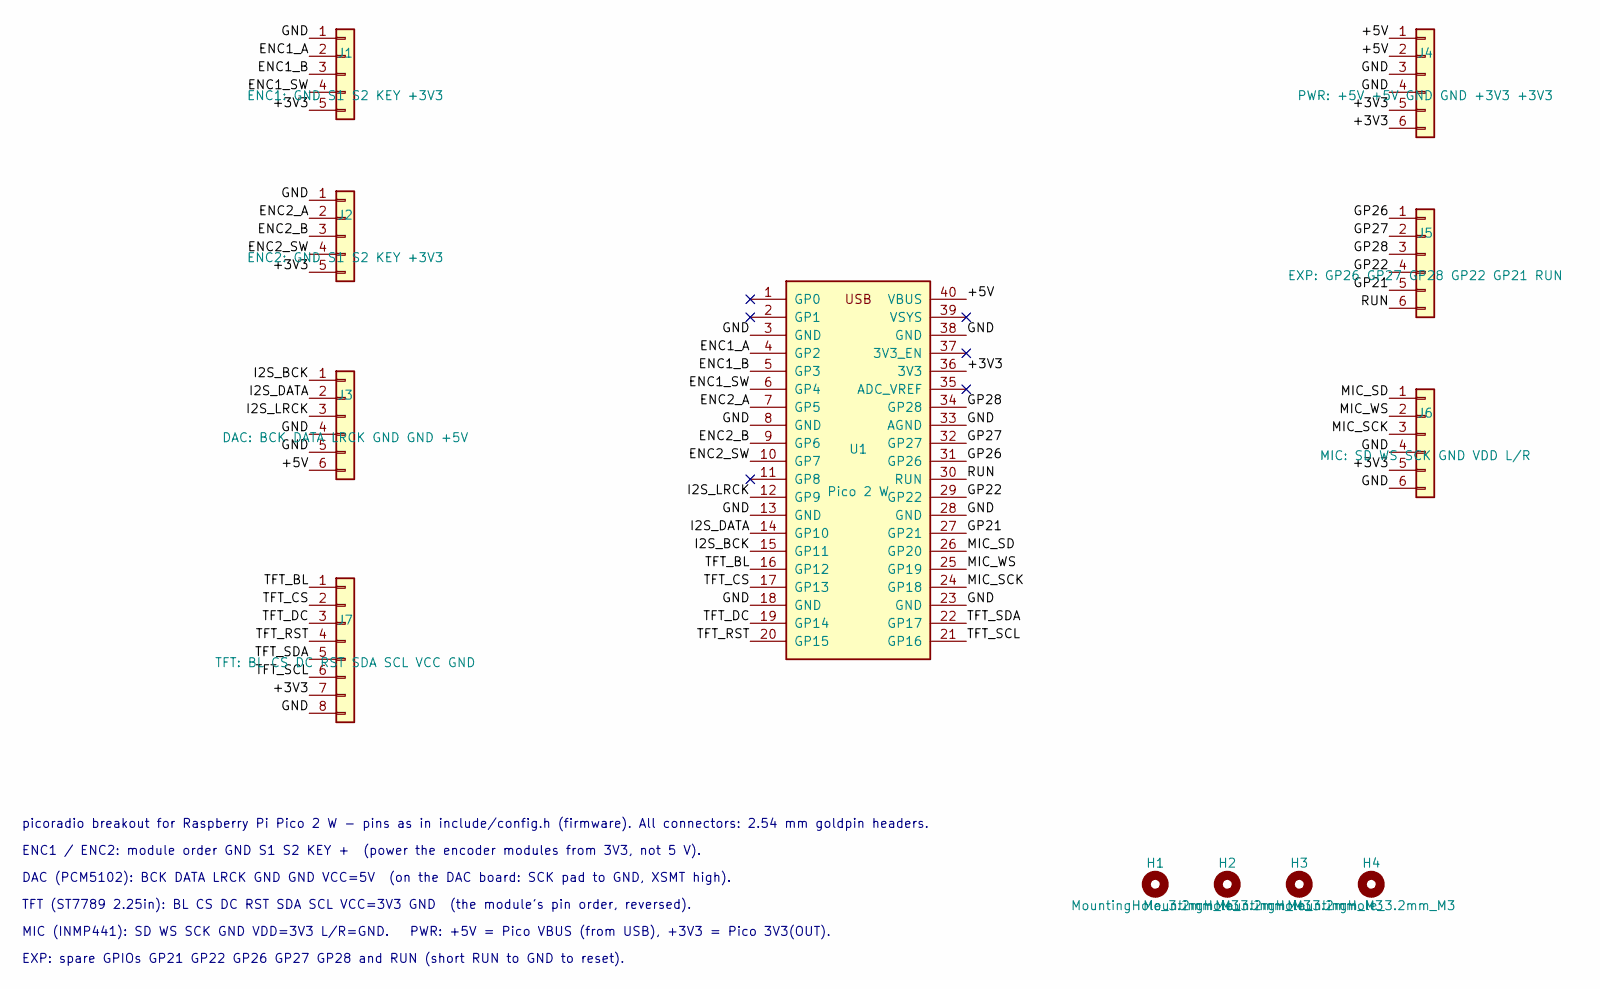
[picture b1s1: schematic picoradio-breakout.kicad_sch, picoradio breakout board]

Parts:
H1, H2, H3, H4: MountingHole_3.2mm_M3
J1: ENC1: GND S1 S2 KEY +3V3; PinHeader_1x05_P2.54mm_Vertical
J2: ENC2: GND S1 S2 KEY +3V3; PinHeader_1x05_P2.54mm_Vertical
J3: DAC: BCK DATA LRCK GND GND +5V; PinHeader_1x06_P2.54mm_Vertical
J4: PWR: +5V +5V GND GND +3V3 +3V3; PinHeader_1x06_P2.54mm_Vertical
J5: EXP: GP26 GP27 GP28 GP22 GP21 RUN; PinHeader_1x06_P2.54mm_Vertical
J6: MIC: SD WS SCK GND VDD L/R; PinHeader_1x06_P2.54mm_Vertical
J7: TFT: BL CS DC RST SDA SCL VCC GND; PinHeader_1x08_P2.54mm_Row
U1: Pico 2 W; RPi_Pico_2W_Socket

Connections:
+3V3: J1.5, J2.5, J4.5, J4.6, J6.5, J7.7, U1.36 (3V3)
+5V: J3.6, J4.1, J4.2, U1.40 (VBUS)
ENC1_A: J1.2, U1.4 (GP2)
ENC1_B: J1.3, U1.5 (GP3)
ENC1_SW: J1.4, U1.6 (GP4)
ENC2_A: J2.2, U1.7 (GP5)
ENC2_B: J2.3, U1.9 (GP6)
ENC2_SW: J2.4, U1.10 (GP7)
GND: J1.1, J2.1, J3.4, J3.5, J4.3, J4.4, J6.4, J6.6, J7.8, U1.3 (GND), U1.8 (GND), U1.13 (GND), U1.18 (GND), U1.23 (GND), U1.28 (GND), U1.33 (AGND), U1.38 (GND)
GP21: J5.5, U1.27 (GP21)
GP22: J5.4, U1.29 (GP22)
GP26: J5.1, U1.31 (GP26)
GP27: J5.2, U1.32 (GP27)
GP28: J5.3, U1.34 (GP28)
I2S_BCK: J3.1, U1.15 (GP11)
I2S_DATA: J3.2, U1.14 (GP10)
I2S_LRCK: J3.3, U1.12 (GP9)
MIC_SCK: J6.3, U1.24 (GP18)
MIC_SD: J6.1, U1.26 (GP20)
MIC_WS: J6.2, U1.25 (GP19)
RUN: J5.6, U1.30 (RUN)
TFT_BL: J7.1, U1.16 (GP12)
TFT_CS: J7.2, U1.17 (GP13)
TFT_DC: J7.3, U1.19 (GP14)
TFT_RST: J7.4, U1.20 (GP15)
TFT_SCL: J7.6, U1.21 (GP16)
TFT_SDA: J7.5, U1.22 (GP17)

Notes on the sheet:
picoradio breakout for Raspberry Pi Pico 2 W - pins as in include/config.h (firmware). All connectors: 2.54 mm goldpin headers.
ENC1 / ENC2: module order GND S1 S2 KEY + (power the encoder modules from 3V3, not 5 V).
DAC (PCM5102): BCK DATA LRCK GND GND VCC=5V (on the DAC board: SCK pad to GND, XSMT high).
TFT (ST7789 2.25in): BL CS DC RST SDA SCL VCC=3V3 GND (the module's pin order, reversed).
MIC (INMP441): SD WS SCK GND VDD=3V3 L/R=GND. PWR: +5V = Pico VBUS (from USB), +3V3 = Pico 3V3(OUT).
EXP: spare GPIOs GP21 GP22 GP26 GP27 GP28 and RUN (short RUN to GND to reset).

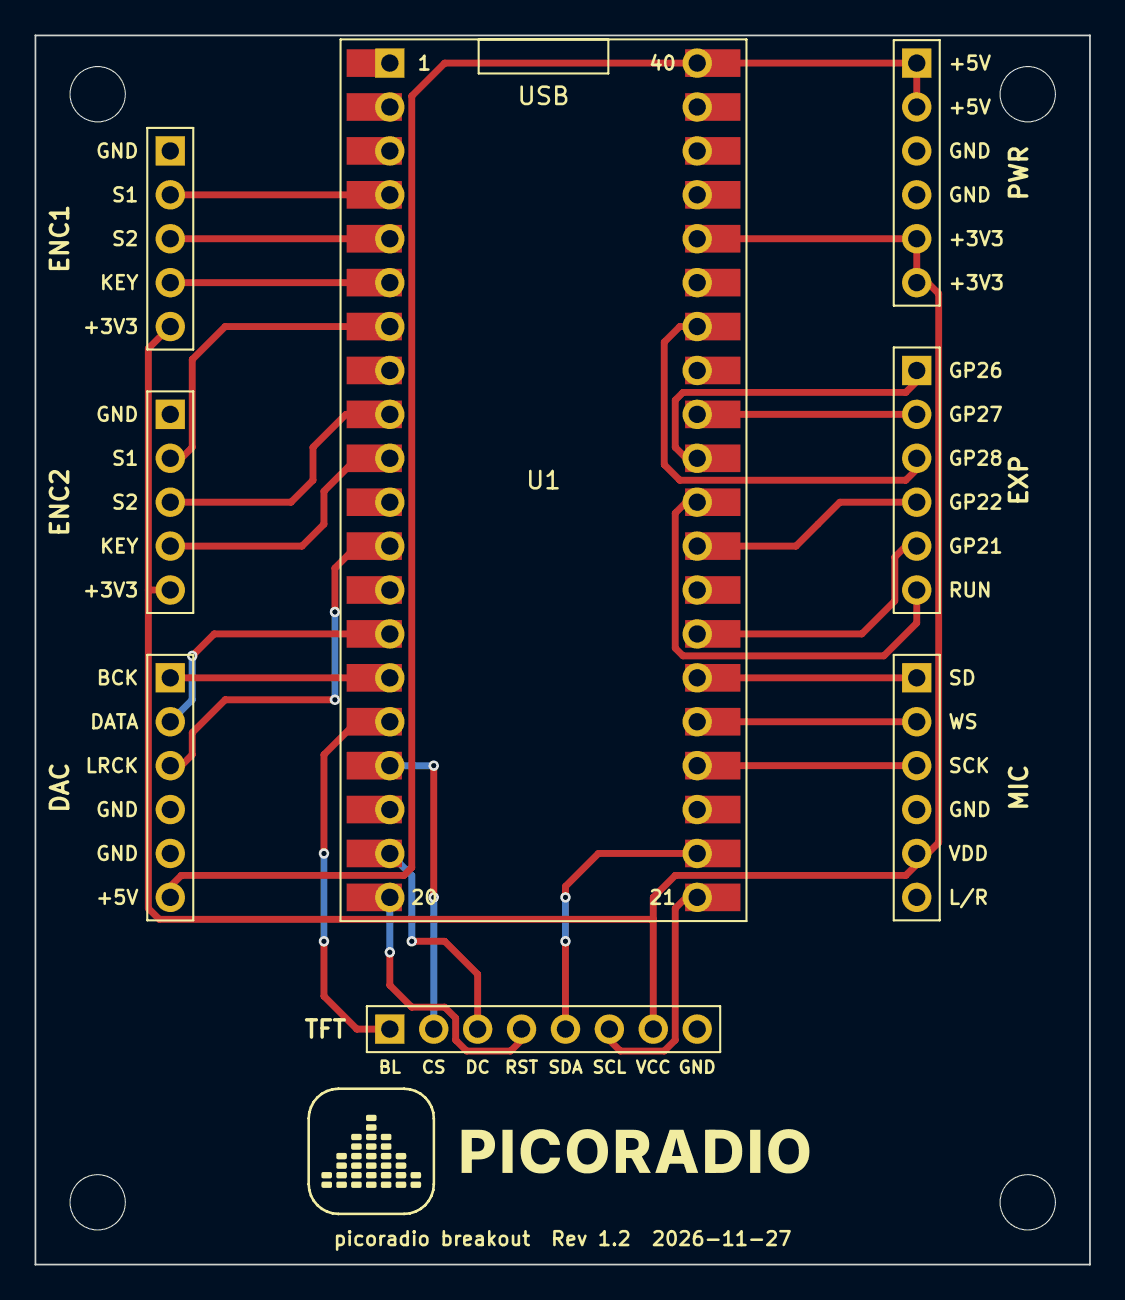
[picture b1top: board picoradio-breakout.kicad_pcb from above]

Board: 2 copper layers, 61.0 x 71.1 mm, 12 parts (0 on the bottom side), 27 nets.

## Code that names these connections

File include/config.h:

#pragma once
/* =====================================================================
 *  Pico 2 W Internet Radio - user configuration
 * ===================================================================== */

/* WiFi, the names, HTTPS checking and the Gemini settings below are only the
 * FACTORY DEFAULTS: change them on the web page (Settings), which saves them in
 * flash. Holding encoder 1 at power-on goes back to these values. */

/* ---------- WiFi ---------- */
/* Set here, or pass at build time: cmake -DWIFI_SSID=... -DWIFI_PASSWORD=... */
#ifndef WIFI_SSID
#define WIFI_SSID       "your-wifi-ssid"
#endif
#ifndef WIFI_PASSWORD
#define WIFI_PASSWORD   "your-wifi-password"
#endif

/* ---------- Web remote ---------- */
/* Control page at http://WEB_HOSTNAME.local/ (or the IP on the info screen) */
#define WEB_HOSTNAME    "picoradio"

/* Setup access point. When no WiFi is set, the network can't be joined
 * AP_AFTER_FAILS times in a row, or encoder 2 is held at power-on, the radio
 * opens its own WiFi network: join it and the settings page opens
 * (or go to http://192.168.4.1). AP_PASSWORD: 8+ characters, "" = open. */
#define AP_SSID         "picoradio"
#define AP_PASSWORD     ""
#define AP_AFTER_FAILS  3
#define AP_IDLE_MIN     10   /* nobody joined for this long: try the saved WiFi again */

/* ---------- HTTPS ---------- */
/* 1 = check station certificates against the bundled roots (ca_roots.h).
 * Set 0 if a station fails with "TLS: unknown cert authority": the audio
 * is public, so skipping the check only risks someone swapping the music. */
#define RADIO_TLS_VERIFY 1

/* ---------- Bluetooth (A2DP sink) ---------- */
#define BT_DEVICE_NAME  "Pico Radio"   /* name shown on the phone */
/* 1 = allow Secure Connections (P-256) pairing. Off by default because it fails
 * with many phones on the CYW43 ("status 0x05"); turn it on if your phone only
 * pairs with it. Forget "Pico Radio" on the phone after changing this. */
#define BT_SECURE_CONNECTIONS 1

/* ---------- Stations (factory defaults) ----------
 * This list is used until you edit stations in the web page; edits are
 * saved in flash and replace it ("Reset to defaults" brings it back).
 * http:// or https:// MP3 / AAC / AAC+ streams, or links to .pls / .m3u
 * playlists (the first stream in the playlist is played). */
typedef struct {
    const char *name;
    const char *url;
} station_t;

static const station_t STATIONS[] __attribute__((unused)) = {
    { "SomaFM Groove Salad", "http://ice1.somafm.com/groovesalad-128-mp3" },
    { "SomaFM Secret Agent", "http://ice1.somafm.com/secretagent-128-mp3" },
    { "SomaFM Indie Pop",    "http://ice1.somafm.com/indiepop-128-mp3" },
    { "SomaFM DEF CON",      "http://ice1.somafm.com/defcon-128-mp3" },
    { "SomaFM Drone Zone",   "http://ice1.somafm.com/dronezone-128-mp3" },
    { "Radio Paradise",      "http://stream.radioparadise.com/mp3-128" },
    { "Groove Salad AAC+",   "https://somafm.com/groovesalad64.pls" },  /* playlist -> HTTPS HE-AAC */
};
#define NUM_STATIONS ((int)(sizeof(STATIONS) / sizeof(STATIONS[0])))

/* ---------- PCM5102 (I2S) ---------- */
#define PIN_I2S_BCLK    11   /* -> BCK  */
#define PIN_I2S_DATA    10   /* -> DATA / DIN */
#define PIN_I2S_LRCK    9    /* -> LRCK / LCK (any pins, any order) */

/* ---------- ST7789 2.25" 76x284 TFT (SPI1) ---------- */
/* Driven by PIO, so any GPIOs work (in the module's pin order here). */
#define PIN_TFT_BL      12   /* backlight (BL / BLK), -1 if tied high */
#define TFT_BL_ACTIVE_LOW 1  /* 1 = the backlight is on when BL is low (some modules) */
#define PIN_TFT_CS      13
#define PIN_TFT_DC      14
#define PIN_TFT_RST     15
#define PIN_TFT_SCK     16   /* SCL */
#define PIN_TFT_MOSI    17   /* SDA */
#define TFT_SPI_HZ      40000000   /* max; the PIO divider rounds down (37.5 MHz at 150 MHz).
                                    * Lower it (e.g. 20000000) if long wires corrupt the picture. */

/* Landscape 284x76. The panel sits in the middle of the 240x320 ST7789 RAM. */
#define TFT_WIDTH       284
#define TFT_HEIGHT      76
#define TFT_X_OFFSET    18
#define TFT_Y_OFFSET    82
#define TFT_MADCTL      0x60 /* MV|MX landscape; use 0xA0 to rotate 180 deg */
#define TFT_BGR         0    /* set 1 if red and blue are swapped */
#define TFT_INVERT      0    /* 1 for panels that show inverted colours (yellow as blue, green as purple) */

/* ---------- Rotary encoders (KY-040 style) ---------- */
/* Encoder 1 = source: Internet Radio / Bluetooth (push: switch/mute) */
/* Encoder 2 = volume; push opens the station list (BT: play/pause)  */
#define PIN_ENC1_A      2
#define PIN_ENC1_B      3
#define PIN_ENC1_SW     4
#define PIN_ENC2_A      5
#define PIN_ENC2_B      6
#define PIN_ENC2_SW     7
#define ENC_STEPS_PER_DETENT 4  /* 4 for most KY-040; 2 if one click needs two clicks */
#define ENC_AB_PULLUP   0    /* 1 = internal pull-ups on S1/S2; 0 = plain input (module has its own pull-ups on +) */
#define ENC1_REVERSE    1
#define ENC2_REVERSE    1

/* ---------- AI voice assistant (Gemini Live API) ---------- */
/* Free API key: https://aistudio.google.com/apikey                   */
/* Set here, or pass at build time: cmake -DGEMINI_API_KEY=...          */
#ifndef GEMINI_API_KEY
#define GEMINI_API_KEY  "your-gemini-api-key"
#endif
#define GEMINI_MODEL    "gemini-3.8-live"
#define GEMINI_VOICE    "Kore"          /* any Gemini TTS voice name */
/* Answer language: a language name in English ("Polish", "English", "German"...)
 * or "auto" to answer in the language you speak. Added to the instructions. */
#define AI_LANGUAGE     "English"
#define AI_GREETING     1               /* 1 = the AI says hello when you switch to it */
#define AI_SYSTEM_PROMPT \
    "You are a voice assistant built into a small internet radio. " \
    "Answer briefly and naturally, usually in 1-3 sentences, " \
    "unless someone asks for more. Don't use lists or formatting."

/* ---------- INMP441 microphone (I2S) ---------- */
#define PIN_MIC_SCK     18   /* -> SCK */
#define PIN_MIC_WS      19   /* -> WS  (must be SCK + 1) */
#define PIN_MIC_SD      20   /* -> SD  ; L/R pin to GND */
#define MIC_GAIN        16   /* 1 = no gain, 16 = +24 dB (INMP441 is quiet) */

/* ---------- Audio ---------- */
#define VOLUME_MAX       32
#define VOLUME_DEFAULT   18
/* Level trim per source, in dB (0 or negative), so the sources sound equally
 * loud at the same volume. Radio stations are mastered much louder than music
 * from a phone, so the radio is turned down a bit. Adjust by ear. */
#define TRIM_RADIO_DB    (-6.0f)
#define TRIM_BT_DB       (0.0f)
#define TRIM_AI_DB       (0.0f)
#define DEFAULT_STATION  0
